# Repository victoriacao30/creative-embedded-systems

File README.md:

# Creative Embedded Systems
Portfolio for Creative Embedded Systems- Spring 2026

## Project 1: Blooming Under Heat
[View Project →](project1-soldering.md)

## Project 2: Wired for Love
[View Project →](pbc-pendant/blogpost.md)

## Project 3: Sonder
[View Project →](ttgoinstallation/blogpost.md)

## Project 4: Inner Child
[View Project →](inner-child/README.md)

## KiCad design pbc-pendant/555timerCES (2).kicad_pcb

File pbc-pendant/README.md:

# Wired for Love :heart:
*A Heart-Shaped 555 Timer LED Pendant*

## Project Overview 
Wired for Love is a heart-shaped PCB pendant powered by a 555 timer that creates a blinking LED. The project explores how functional circuitry can be shaped into expressive, creative art. Designed for Valentine’s Day, the blinking LED acts as a small “heartbeat.”

This project was created as part of a PCB fabrication assignment focused on layout design, CNC milling, and soldering. 

## Components: 
- TL555 timer
- 1x LED
- Resistor R1 and R2 (timing resistors), R3 (LED current-limiting resistor)
- Capacitors C1 (timing capacitor), C2 (10nF decoupling capacitor)
- 3.7V coin cell battery
- Coin cell battery holder

## Building Process:
1. Design schematic in KiCad.
2. Create heart-shaped board outline using Edge.Cuts.
3. Route traces to fit within the heart form.
4. Export files for CNC milling.
5. Milled PCB.
6. Soldered all components.
7. Powered using a 3V coin cell battery.

## Visual Documentation:

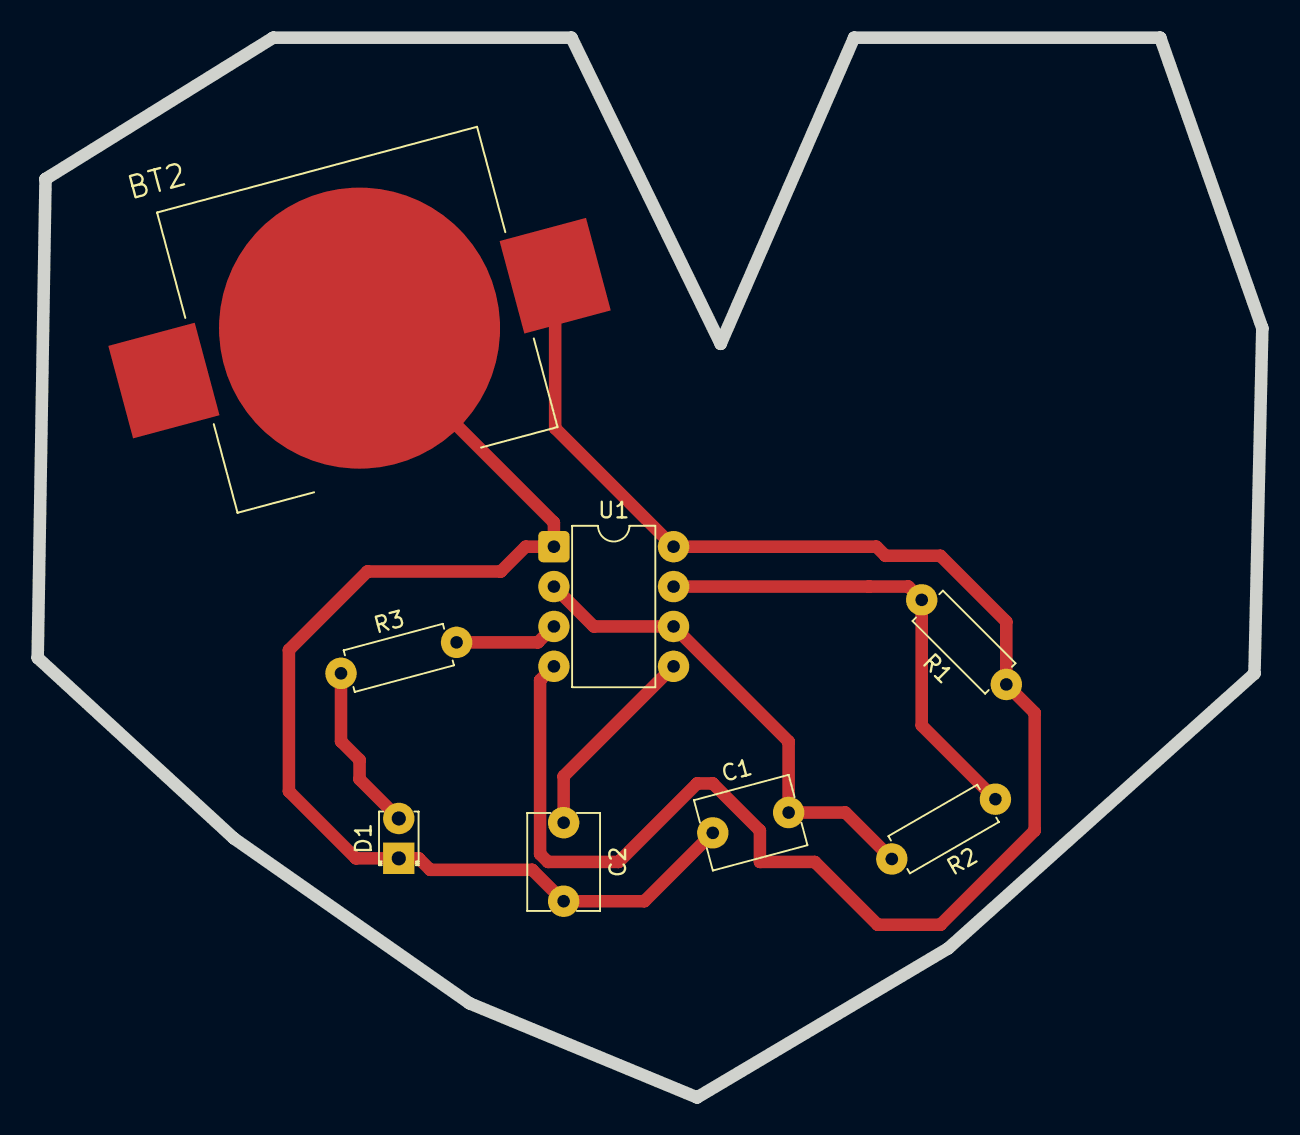
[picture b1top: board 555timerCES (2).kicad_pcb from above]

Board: 2 copper layers, 78.0 x 67.5 mm, 8 parts (0 on the bottom side), 7 nets.

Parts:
BT2: BAT-HLD-003-SMT; BAT_BAT-HLD-003-SMT
C1: C; C_Disc_D6.0mm_W4.4mm_P5.00mm
C2: 10n; C_Disc_D6.0mm_W4.4mm_P5.00mm
D1: LED; LED_D1.8mm_W3.3mm_H2.4mm
R1, R2, R3: R; R_Axial_DIN0207_L6.3mm_D2.5mm_P7.62mm_Horizontal
U1: TLC555xP; DIP-8_W7.62mm

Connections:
+3V0: BT2.P1, BT2.P2, R1.1, U1.4 (R), U1.8 (VCC)
GND: BT2.N, C1.1, C2.2, D1.1 (K), U1.1 (GND)
unnamed: D1.2 (A), R3.1
unnamed: C2.1, U1.5 (CV)
unnamed: R1.2, R2.1, U1.7 (DIS)
unnamed: R3.2, U1.3 (Q)
unnamed: C1.2, R2.2, U1.2 (TR), U1.6 (THR)

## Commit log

2026-01-28 Create Project1- Soldering
2026-01-28 Rename Project1- Soldering to project1-soldering.md
2026-01-28 Add project overview for 'Blooming Under Heat'
    Added project description and details about the materials used.
2026-01-28 hero image
2026-01-29 reflection and images
2026-01-29 edit wording
2026-01-29 connect to project1
2026-01-29 title
2026-01-29 change header
2026-02-12 Create PBC
2026-02-12 Rename README.md to HomePage.md
2026-02-12 Rename HomePage.md to README.md
2026-02-12 Rename PBC to pbc-pendant/README.md
2026-02-12 Enhance README with project inspiration and insights
    Added personal reflections on the project and soldering experience.
2026-02-12 Delete project introduction and personal reflections
    Removed personal narrative from the README file.
2026-02-12 Change blog post title to 'Wired for Love'
    Updated the blog post title and added a sparkly heart emoji.
2026-02-12 Update blogpost title emoji from sparkling to revolving
2026-02-12 Enhance README with project details and instructions
    Added project overview, components, and building process details to the README.
2026-02-12 Create design-files
2026-02-12 Rename 555timerCES (1).kicad_pro to 555timerCES.kicad_pro
2026-02-12 Rename 555timerCES (2).kicad_pcb to 555timerCES.kicad_pcb
2026-02-12 Revise demo video section in blogpost.md
    Updated demo video link and added a description.
2026-02-12 Correct demo video link formatting
    Fixed formatting of the demo video link.
2026-02-12 Correct video link and update demo video section
    Fixed the video link formatting and updated the demo video section.
2026-02-12 Update demo video link format in blogpost.md
    Removed image link and changed it to a text link for the demo video.
2026-02-12 Rename front light.jpeg to frontlight.jpeg
2026-02-12 Revise demo video section for clarity and engagement
    Updated the demo video section with a more engaging title and link format.
2026-02-12 Revise blogpost with additional images and reflections
    Updated blogpost with new images and improved sections.
2026-02-12 Add images to README for visual documentation
    Added visual documentation images to the README.
2026-02-12 Add Project 2: Wired to Love to README
2026-02-12 Fix project title from 'Wired to Love' to 'Wired for Love'
2026-02-12 Add additional images to README for documentation
2026-02-12 Update image reference for solder file
    Replace lowercased 'solder.heic' with 'solder.HEIC'.
2026-03-02 Create project3-ttgodisplay
2026-03-02 Add main.cpp for Arduino TFT display control
2026-03-02 Add blog post about ESP32 installation project
    Added a blog post detailing the ESP32 installation project inspired by the concept of sonder, discussing challenges faced and artistic decisions made.
2026-03-02 Fix demo video link formatting in blogpost.md
2026-03-02 Fix demo video link in blogpost.md
    Corrected the demo video link format in the blog post.
2026-03-02 Revise README with project details and requirements
    Updated project description and requirements in README.
2026-03-02 Add Project 3: Sonder to README
2026-03-06 comments
2026-04-06 Create README.md for Inner Child project
    Added README.md with project details, technical process, and installation instructions.
2026-04-06 Update link for Inner Child project
2026-04-21 edit
    Revised reflection section to express excitement about the installation experience.
